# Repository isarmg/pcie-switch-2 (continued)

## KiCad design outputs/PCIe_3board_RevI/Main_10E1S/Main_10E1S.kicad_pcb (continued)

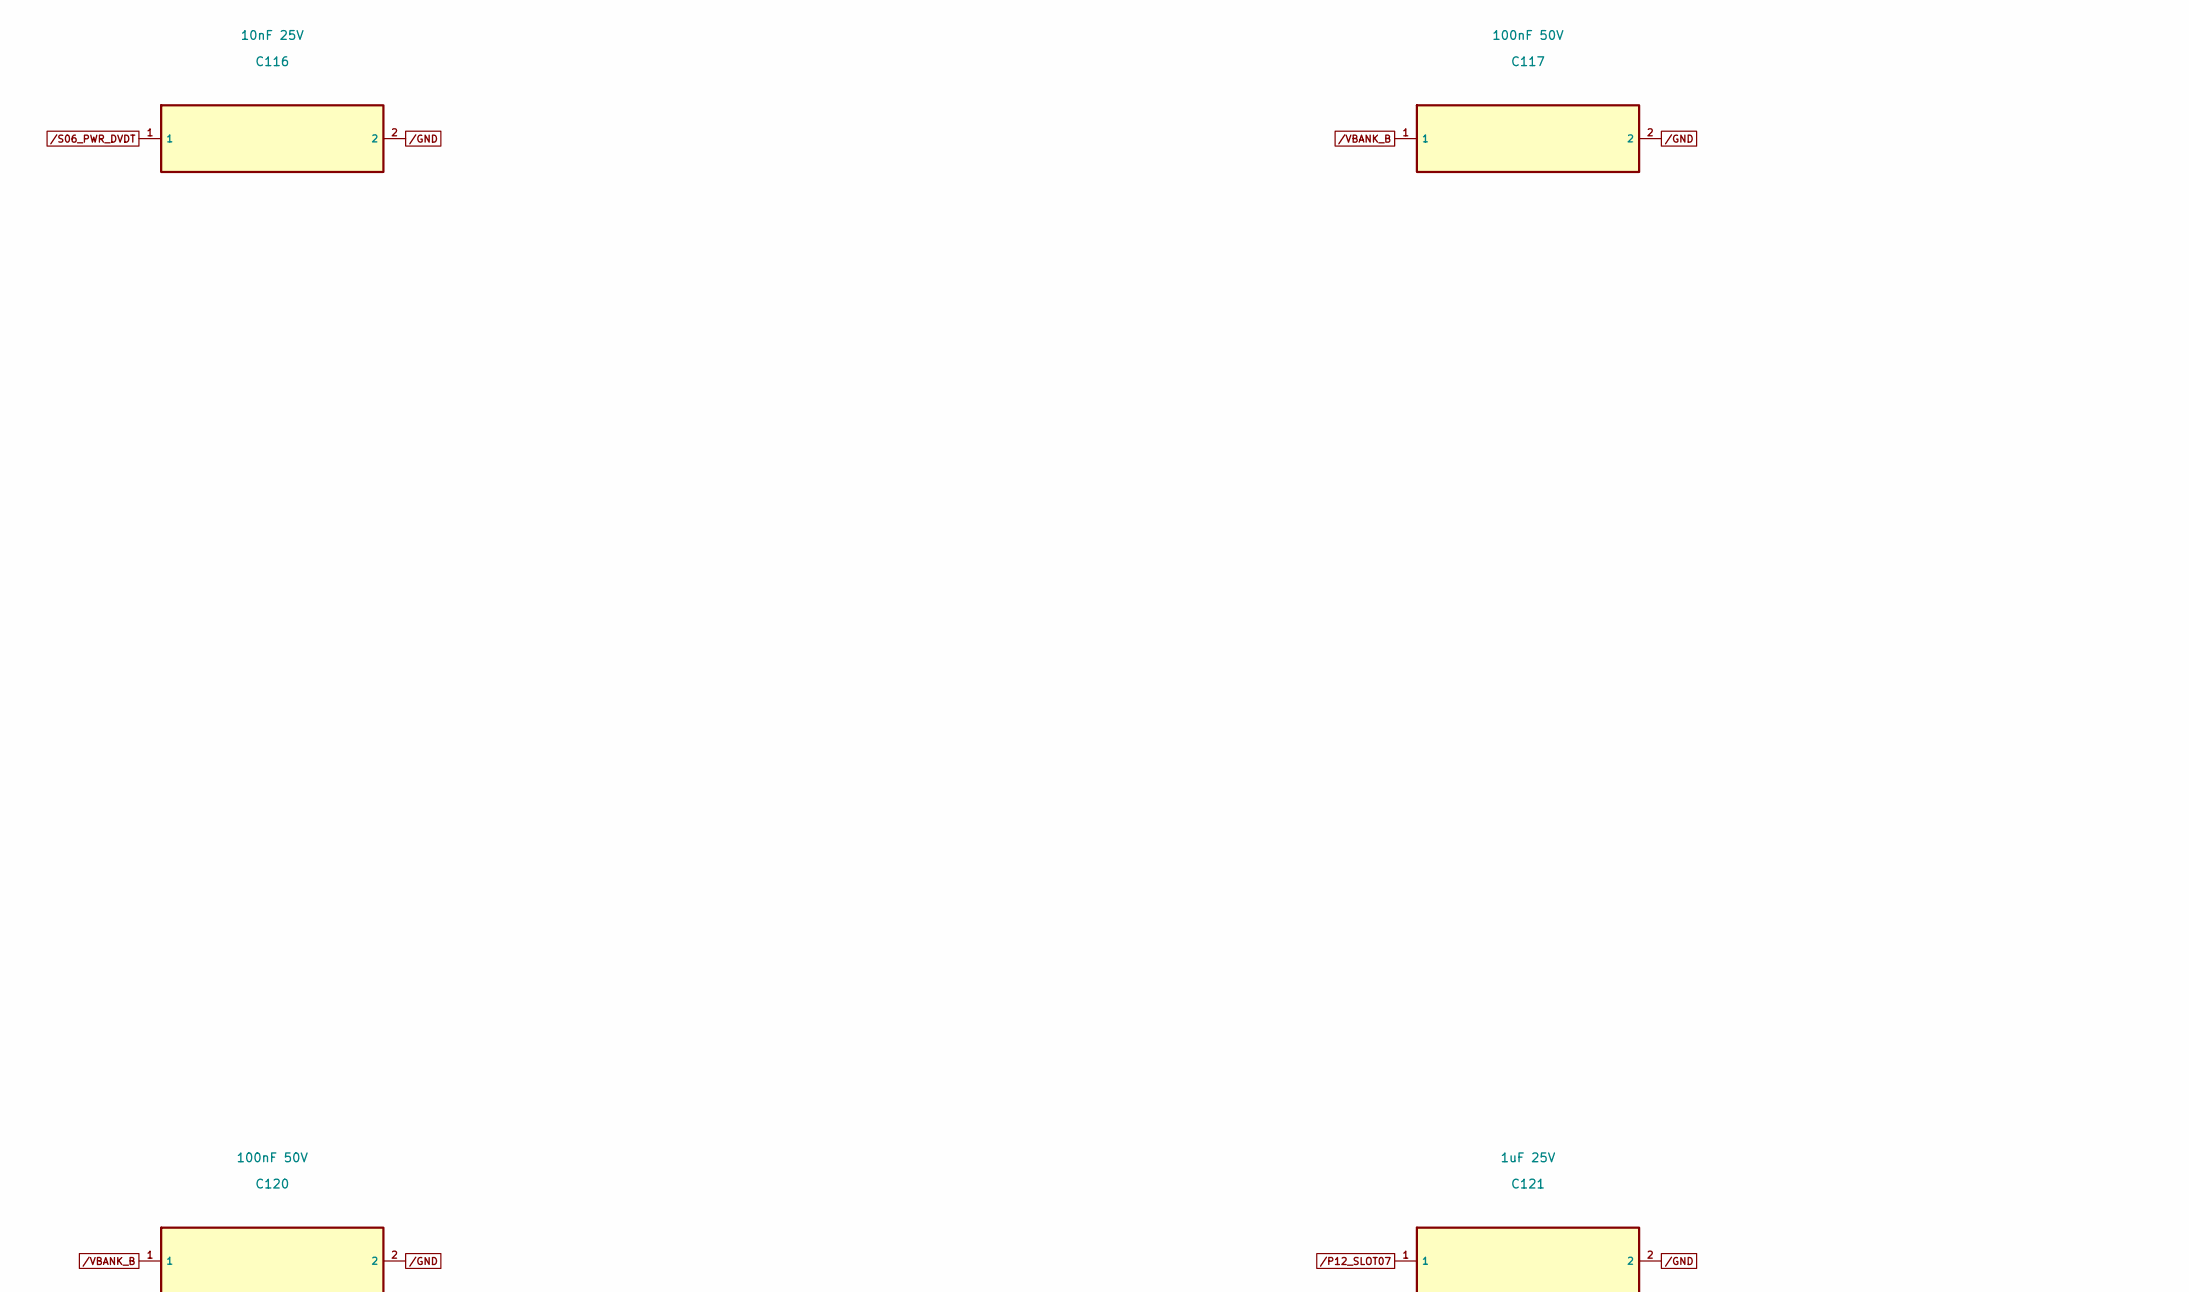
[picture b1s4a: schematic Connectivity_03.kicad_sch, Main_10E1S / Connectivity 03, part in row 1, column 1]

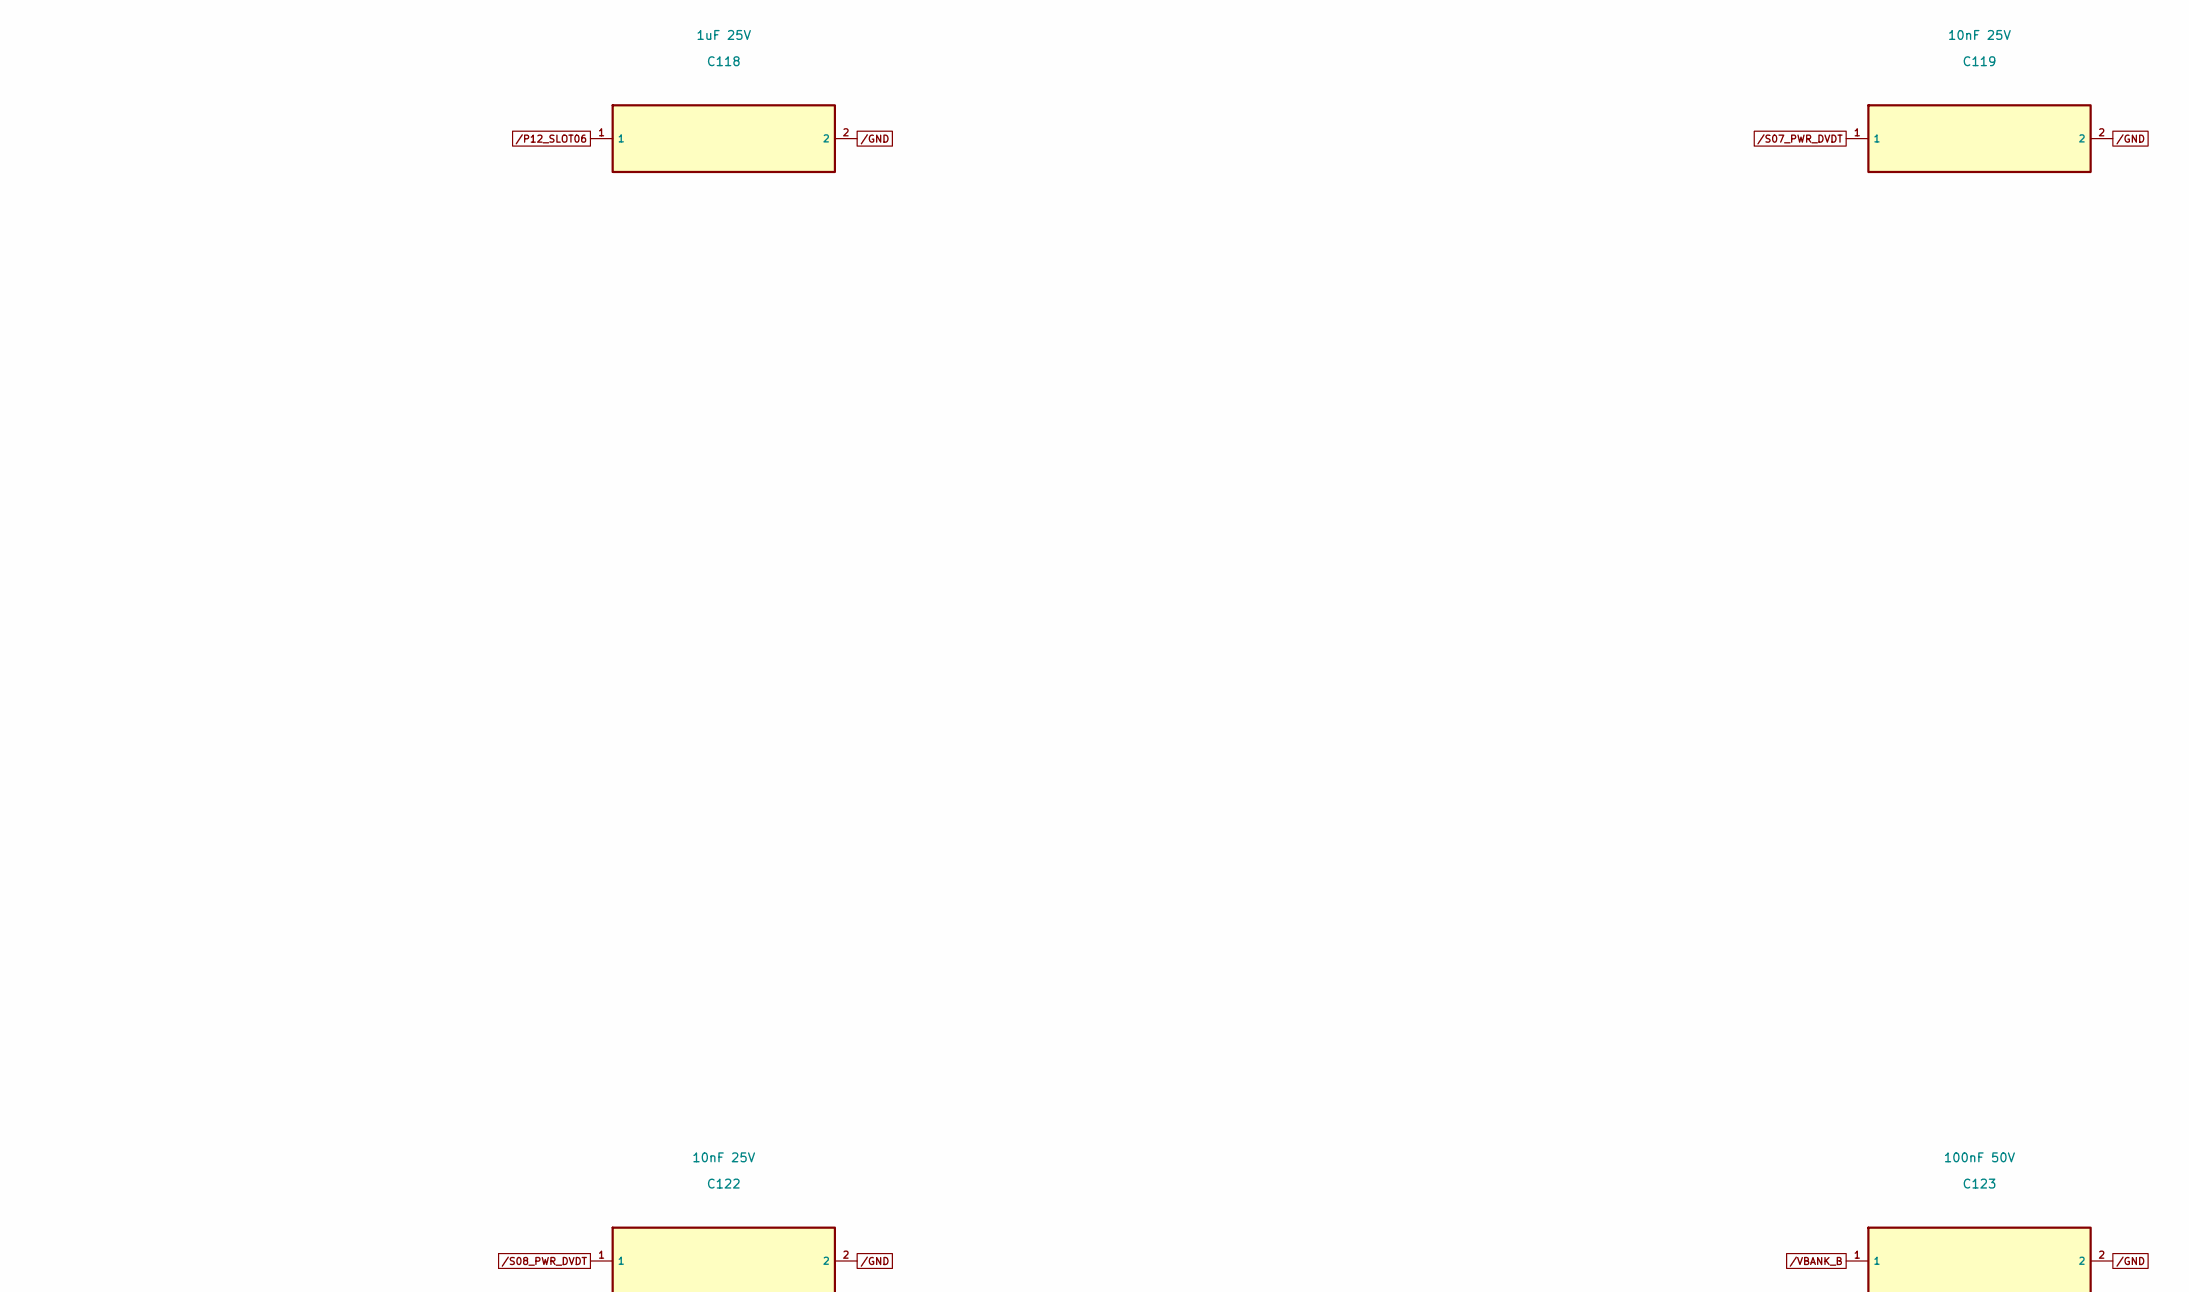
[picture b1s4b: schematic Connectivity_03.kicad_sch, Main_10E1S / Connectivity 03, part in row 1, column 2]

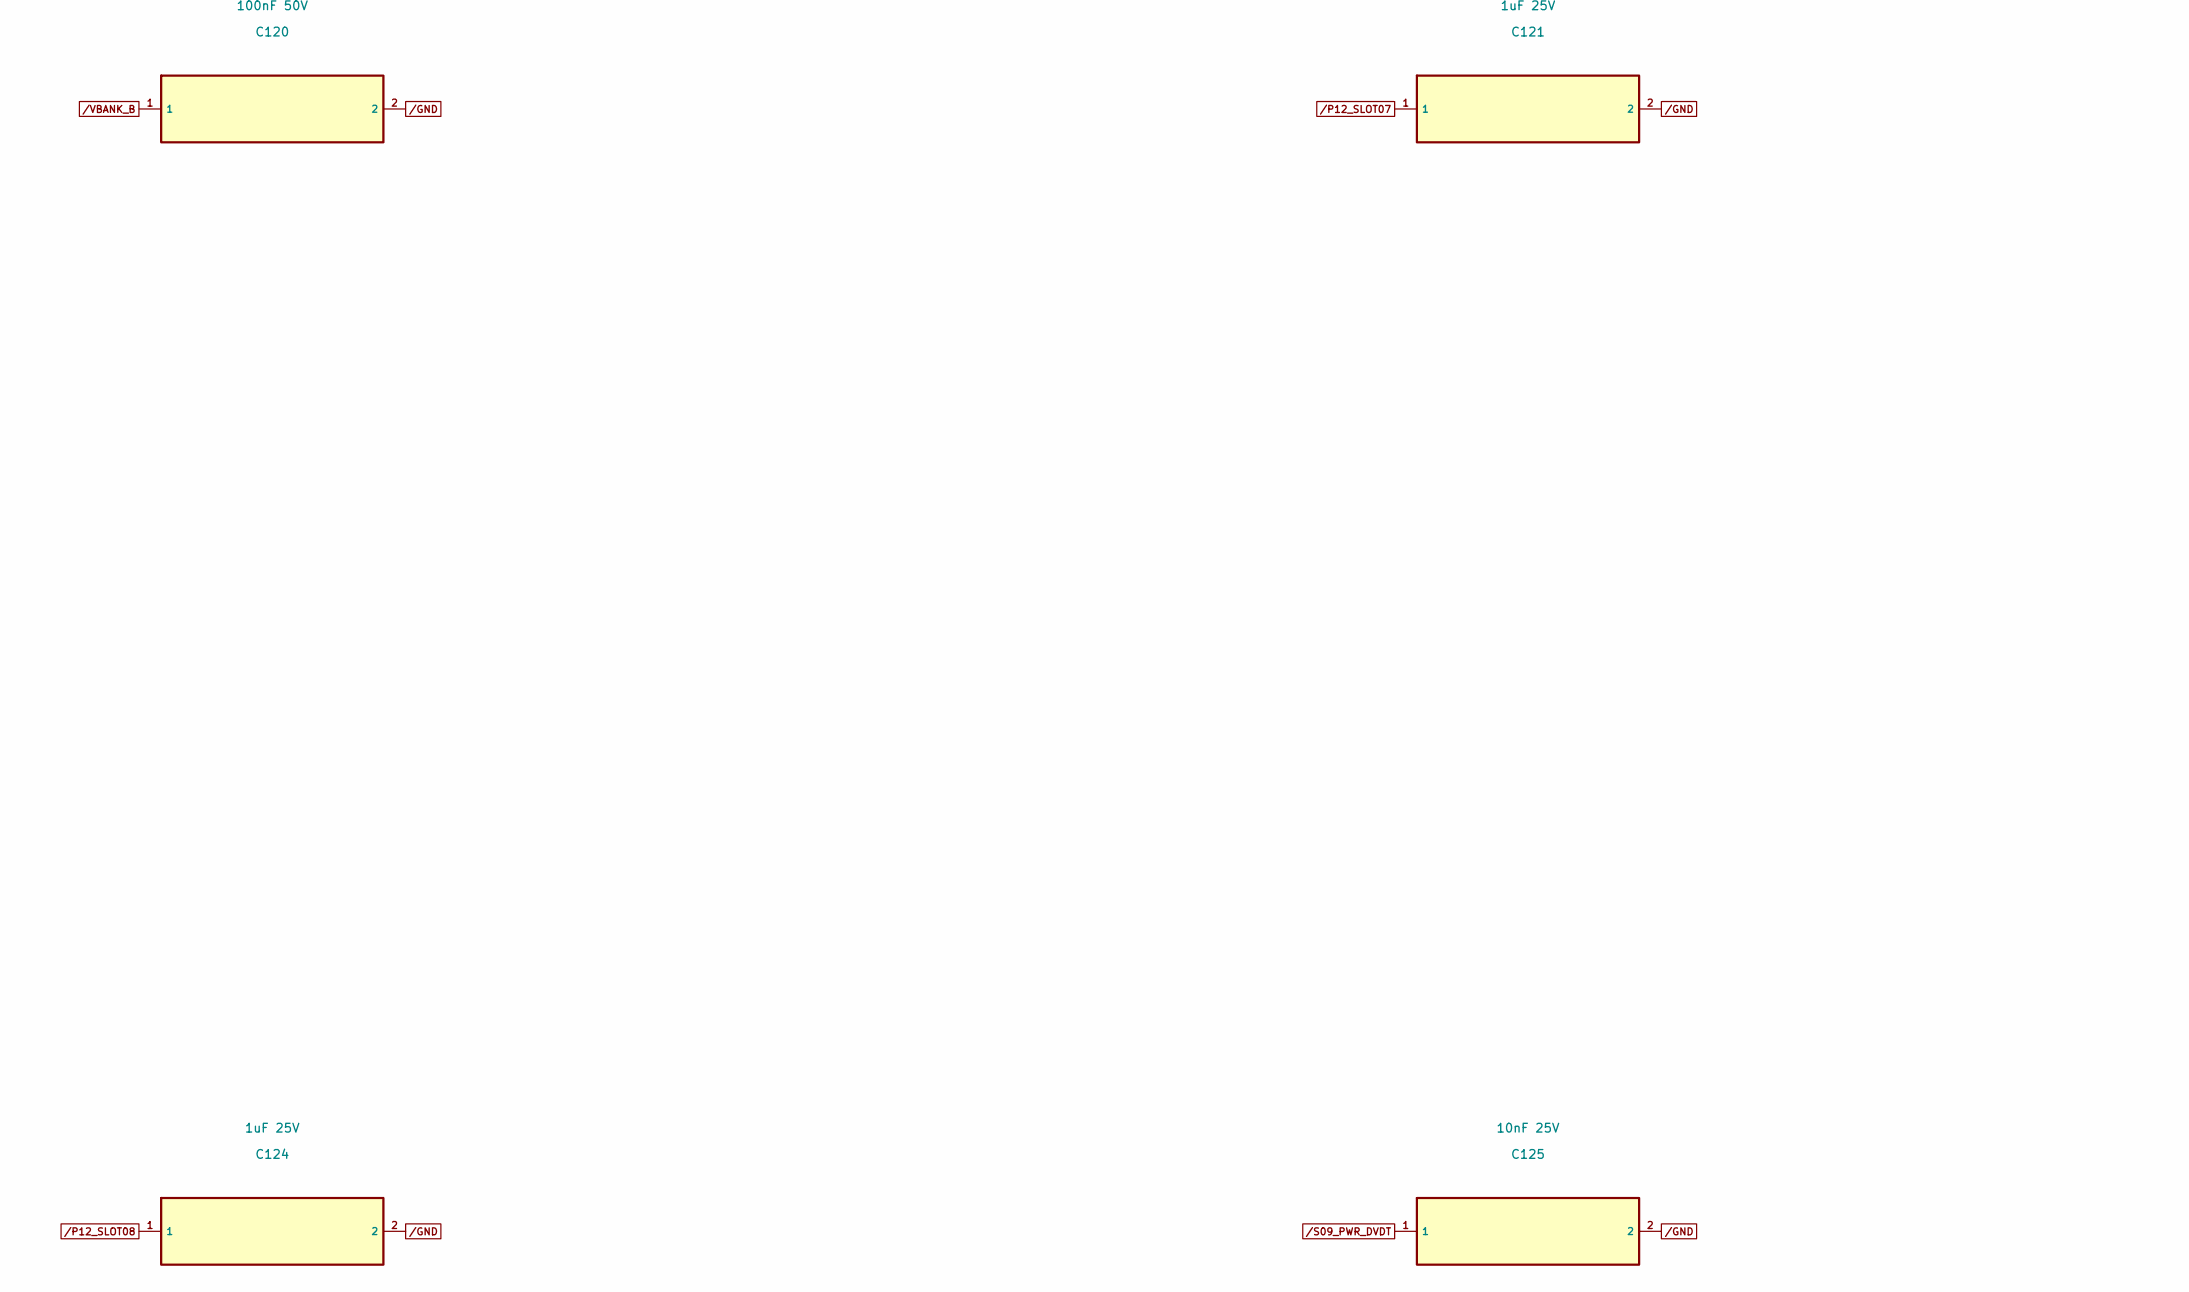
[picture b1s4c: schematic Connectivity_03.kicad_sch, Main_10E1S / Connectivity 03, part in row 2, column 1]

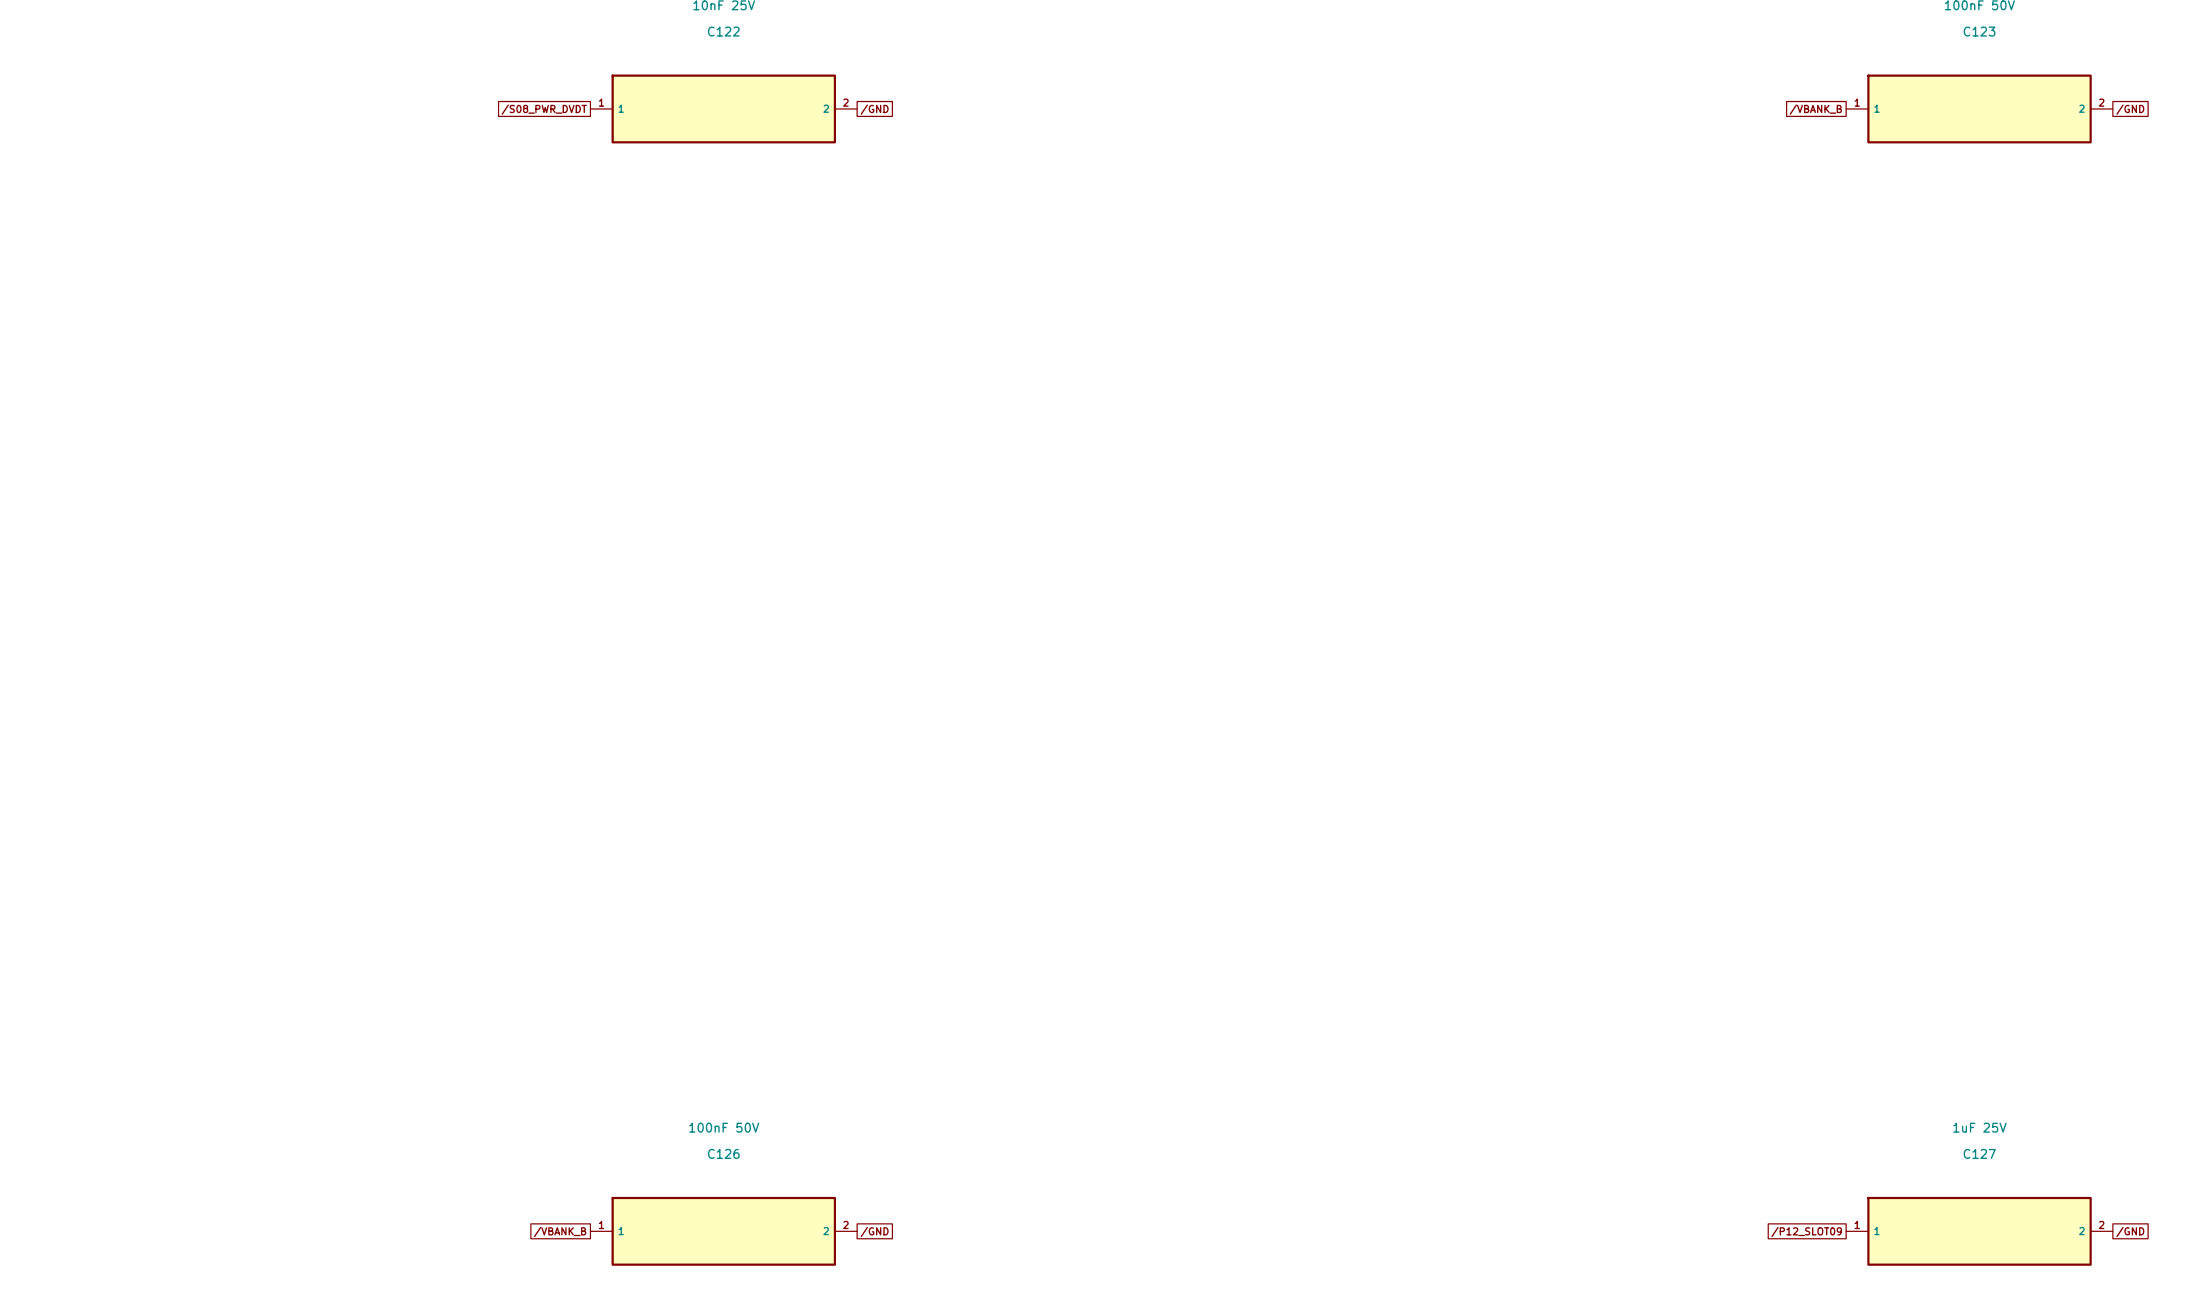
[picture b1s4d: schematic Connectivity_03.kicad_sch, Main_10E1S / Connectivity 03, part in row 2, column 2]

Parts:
C116, C119, C122, C125: 10nF 25V; C_0402_1005Metric
C117, C120, C123, C126: 100nF 50V; C_0603_1608Metric
C118, C121, C124, C127: 1uF 25V; C_0603_1608Metric

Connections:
/GND: C116.2, C117.2, C118.2, C119.2, C120.2, C121.2, C122.2, C123.2, C124.2, C125.2, C126.2, C127.2; also elsewhere on the board
/P12_SLOT06: C118.1; also elsewhere on the board
/P12_SLOT07: C121.1; also elsewhere on the board
/P12_SLOT08: C124.1; also elsewhere on the board
/P12_SLOT09: C127.1; also elsewhere on the board
/S06_PWR_DVDT: C116.1; also elsewhere on the board
/S07_PWR_DVDT: C119.1; also elsewhere on the board
/S08_PWR_DVDT: C122.1; also elsewhere on the board
/S09_PWR_DVDT: C125.1; also elsewhere on the board
/VBANK_B: C117.1, C120.1, C123.1, C126.1; also elsewhere on the board
